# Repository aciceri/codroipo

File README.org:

* Codroipo

~codroipo~ is my personalized [[https://github.com/beekeeb/Allium58][Allium58]].
Basically I simply removed the OLED display and everything related to wired build, sligthly moved some components and added some cosmetics.

** Build the firmware

#+BEGIN_SRC sh
nix build github:aciceri/codroipo#firmware
#+END_SRC

** Flash the firmware

#+BEGIN_SRC sh
nix run github:aciceri/codroipo#flash
#+END_SRC

** Pictures

[[./pics/1.jpg]]
[[./pics/2.jpg]]
[[./pics/3.jpg]]
[[./pics/4.jpg]]
[[./pics/5.jpg]]
[[./pics/6.jpg]]
[[./pics/7.jpg]]

** Aknowledgements

- [[https://github.com/beekeeb][beekeeb]] for the original [[https://github.com/beekeeb/Allium58][Allium58]]
- [[https://github.com/kata0510][kata0510]] for the original [[https://github.com/kata0510/Lily58][Lily58]] design which the Allium58 is based on
- [[https://github.com/lilyinstarlight][lilyinstarlight]] for [[https://github.com/lilyinstarlight/zmk-nix][zmk-nix]] which allows building [[https://zmk.dev/l][ZMK]] firmware with Nix
- [[https://www.fiverr.com/jorgetukuy][jorgetukuy]] for changing the original Allium58 case according to my specifications

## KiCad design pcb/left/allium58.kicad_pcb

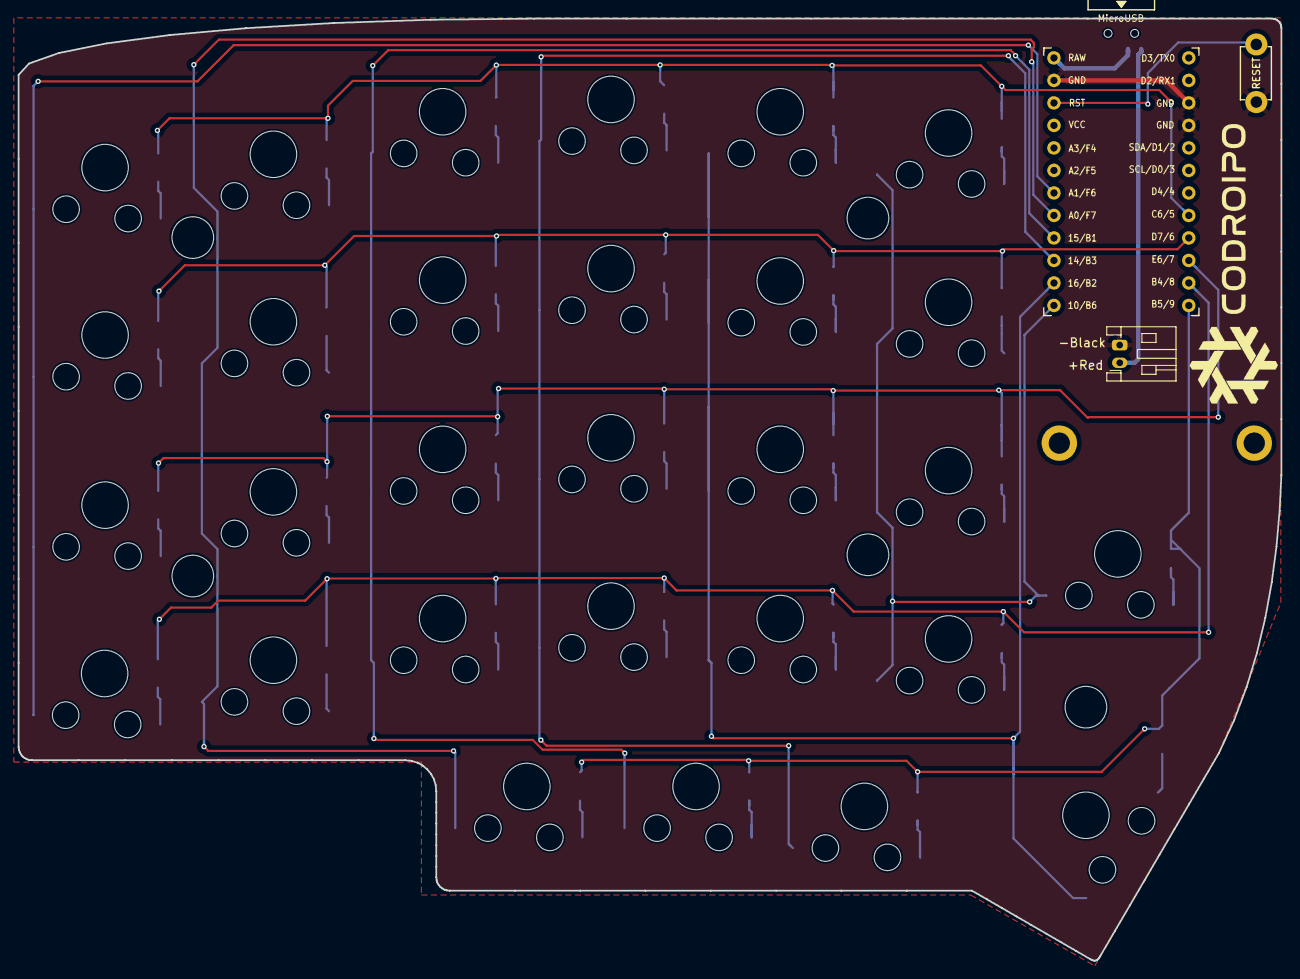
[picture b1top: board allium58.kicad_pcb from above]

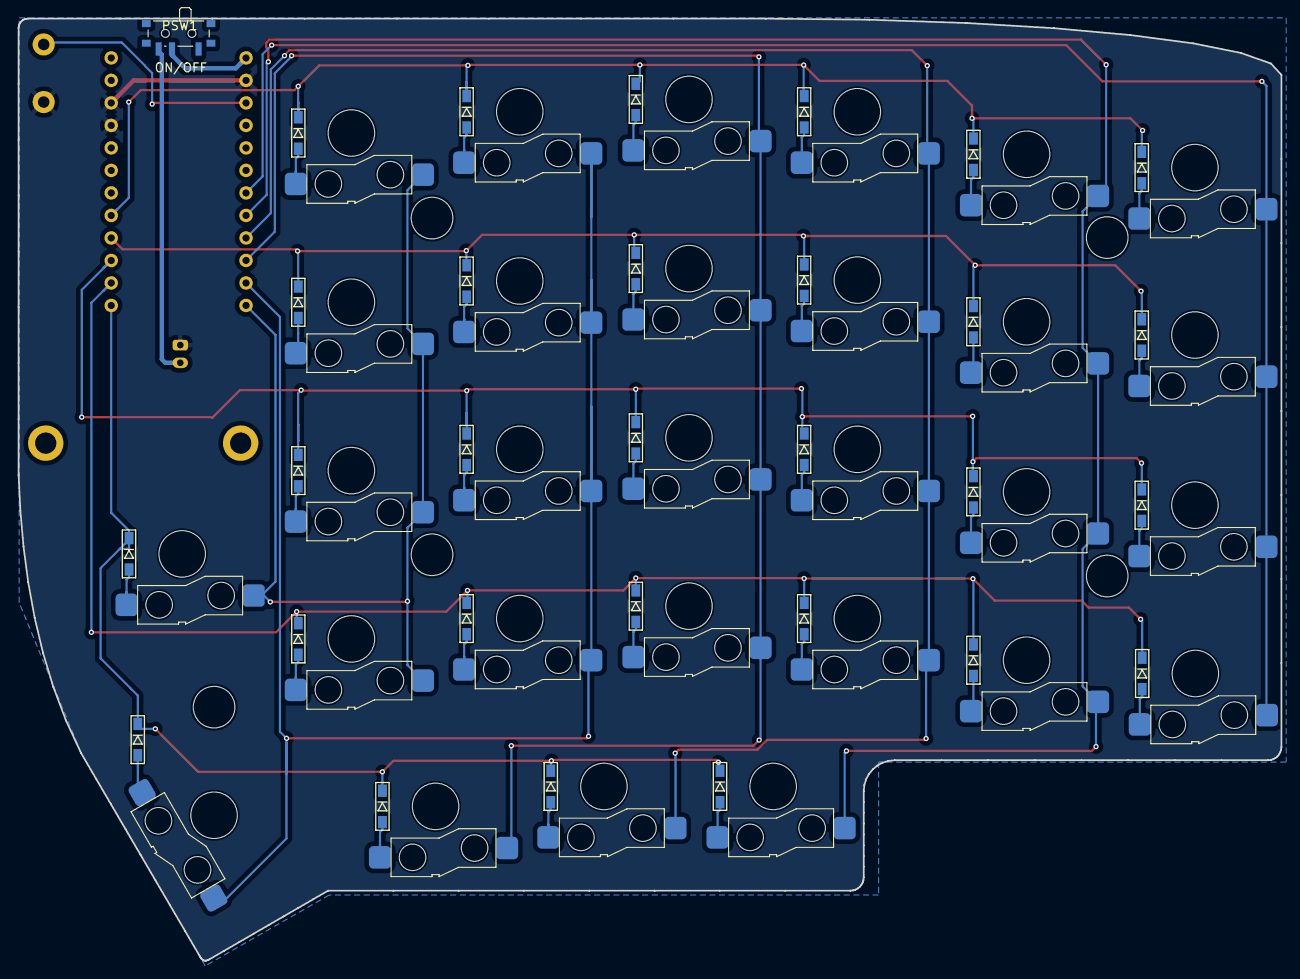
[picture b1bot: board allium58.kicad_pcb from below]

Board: 2 copper layers, 142.5 x 106.3 mm, 69 parts (37 on the bottom side), 44 nets.

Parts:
BATJ1: Conn_01x02_Female; JST_PH_S2B-PH-K_1x02_P2.00mm_Horizontal
D1, D2, D3, D4, D5, D6, D7, D8, D9, D10, D11, D12, D13, D14, D15, D16, D17, D18, D19, D20, D21, D22, D23, D24, D25, D26, D27, D28, D29: D; D3_SMD_v2
PSW1: SW_SPST; SW_SPDT_PCM12
RSW1: SW_RST; TACT_SWITCH_TVBP06
SW1, SW2, SW3, SW4, SW5, SW6, SW7, SW8, SW9, SW10, SW11, SW12, SW13, SW14, SW15, SW16, SW17, SW18, SW19, SW20, SW21, SW22, SW23, SW24, SW25, SW26, SW27, SW28, SW29: SW_PUSH; SW_Gateron_LowProfile_HotSwap
TH1, TH2: HOLE; M2_HOLE_PCB
TH3, TH4, TH5, TH6, TH7: HOLE; HOLE_M2_TH
U1: ProMicro; ProMicro_v3

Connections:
+BATT: BATJ1.1, PSW1.3 (C)
GND: BATJ1.2, RSW1.1, U1.3 (GND), U1.4 (GND), U1.23 (GND)
unnamed: D1.2 (A), SW1.2
unnamed: D2.2 (A), SW2.2
unnamed: D3.2 (A), SW3.2
unnamed: D4.2 (A), SW4.2
unnamed: D5.2 (A), SW5.2
unnamed: D6.2 (A), SW6.2
unnamed: D7.2 (A), SW7.2
unnamed: D8.2 (A), SW8.2
unnamed: D9.2 (A), SW9.2
unnamed: D10.2 (A), SW10.2
unnamed: D11.2 (A), SW11.2
unnamed: D12.2 (A), SW12.2
unnamed: D13.2 (A), SW13.2
unnamed: D14.2 (A), SW14.2
unnamed: D15.2 (A), SW15.2
unnamed: D16.2 (A), SW16.2
unnamed: D17.2 (A), SW17.2
unnamed: D18.2 (A), SW18.2
unnamed: D19.2 (A), SW19.2
unnamed: D20.2 (A), SW20.2
unnamed: D21.2 (A), SW21.2
unnamed: D22.2 (A), SW22.2
unnamed: D23.2 (A), SW23.2
unnamed: D24.2 (A), SW24.2
unnamed: D25.2 (A), SW25.2
unnamed: D26.2 (A), SW26.2
unnamed: D27.2 (A), SW27.2
unnamed: D28.2 (A), SW28.2
unnamed: D29.2 (A), SW29.2
RESET: RSW1.2, U1.22 (RST)
col0: SW6.1, SW12.1, SW18.1, SW24.1, U1.18 (A1(PF6))
col1: SW5.1, SW11.1, SW17.1, SW23.1, SW29.1, U1.17 (A0(PF7))
col2: SW4.1, SW10.1, SW16.1, SW22.1, SW28.1, U1.16 (D15(PB1))
col3: SW3.1, SW9.1, SW15.1, SW21.1, SW27.1, U1.15 (D14(PB3))
col4: SW2.1, SW8.1, SW14.1, SW20.1, SW26.1, U1.14 (D16(PB2))
col5: SW1.1, SW7.1, SW13.1, SW19.1, SW25.1, U1.13 (D10(PB6))
raw: PSW1.2 (B), U1.24 (RAW)
row0: D1.1 (K), D2.1 (K), D3.1 (K), D4.1 (K), D5.1 (K), D6.1 (K), U1.8 (D5(PC6))
row1: D7.1 (K), D8.1 (K), D9.1 (K), D10.1 (K), D11.1 (K), D12.1 (K), U1.9 (D6(PD7))
row2: D13.1 (K), D14.1 (K), D15.1 (K), D16.1 (K), D17.1 (K), D18.1 (K), U1.10 (D7(PE6))
row3: D19.1 (K), D20.1 (K), D21.1 (K), D22.1 (K), D23.1 (K), D24.1 (K), U1.11 (D8(PB4))
row4: D25.1 (K), D26.1 (K), D27.1 (K), D28.1 (K), D29.1 (K), U1.12 (D9(PB5))

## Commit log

2024-04-30 README with pictures
2024-05-23 Bump `zmk-nix`
2024-05-23 Reset config uf2
2024-05-30 Bump deps
2024-05-30 Enable split battery monitoring
